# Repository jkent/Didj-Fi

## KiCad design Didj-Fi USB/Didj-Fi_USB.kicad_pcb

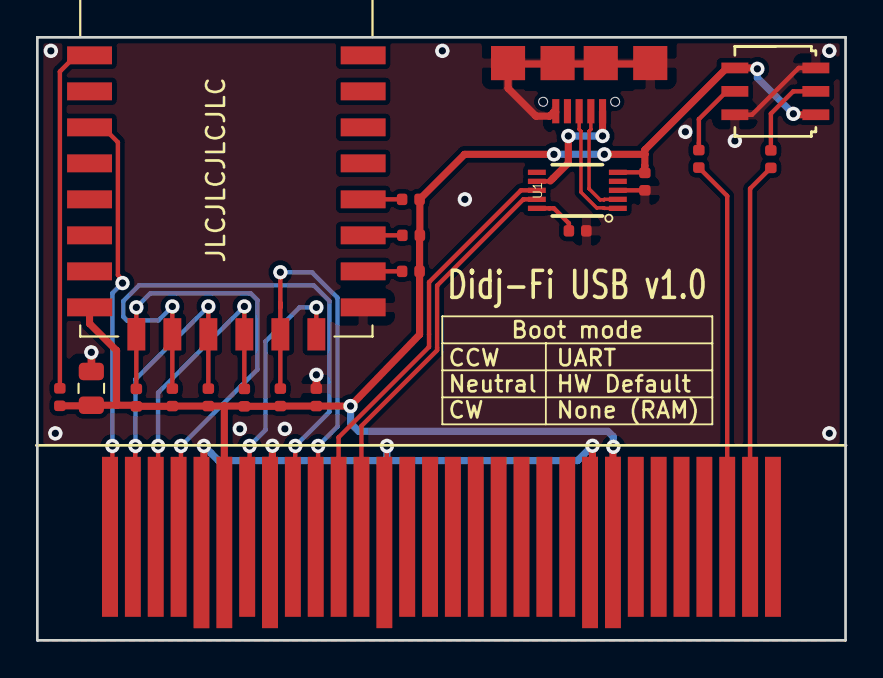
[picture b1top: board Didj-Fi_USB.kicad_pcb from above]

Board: 2 copper layers, 44.9 x 33.5 mm, 20 parts (0 on the bottom side), 23 nets.

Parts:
C1, C2, C4: 0.1u; C_0402_1005Metric
C3: 22u; C_0805_2012Metric
J1: didj_cart
J3: USB_B_Micro; C40942
R1, R3, R4, R5, R7, R8, R9, R11: 10k; R_0402_1005Metric
R2, R10: 4.7k; R_0402_1005Metric
R6: 3k; R_0402_1005Metric
S1: CS-4-22YA; cs-4
U1: CH340E; MSOP10
U2: ESP-12F; ESP-12E

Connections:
+3V3: C1.1, C3.1, C4.1, J1.6, J1.23, R1.1, R3.1, R4.1, R5.1, R6.1, R7.1, R8.1, R9.1, R11.1, S1.2, S1.~2, U1.5, U2.8
/CLK: J1.7, U2.14
/CMD: J1.4, R6.2, U2.9
/D5: J1.28, R2.2
/D6: J1.29, R10.1
/D+: J3.3, U1.1
/D-: J3.2, U1.2
/DAT0: J1.9, R3.2, U2.10
/DAT1: J1.10, R7.2, U2.13
/DAT2: J1.2, R4.2, U2.11
/DAT3: J1.3, R8.2, U2.12
/EN: J1.1, U2.3
/GPIO0: R11.2, U2.18
/GPIO2: R1.2, U2.17
/GPIO15: R9.2, U2.16
/RX: J1.11, U1.8
/TX: J1.12, U1.9
/V3: C2.1, U1.10
/~RST: R5.2, U2.1
GND: C1.2, C2.2, C3.2, C4.2, J1.5, J1.8, J1.13, J1.22, J3.5, J3.6, S1.1, S1.~1, U1.3, U2.15
unnamed: R2.1, S1.C
unnamed: R10.2, S1.~C
VBUS: J3.1, U1.7

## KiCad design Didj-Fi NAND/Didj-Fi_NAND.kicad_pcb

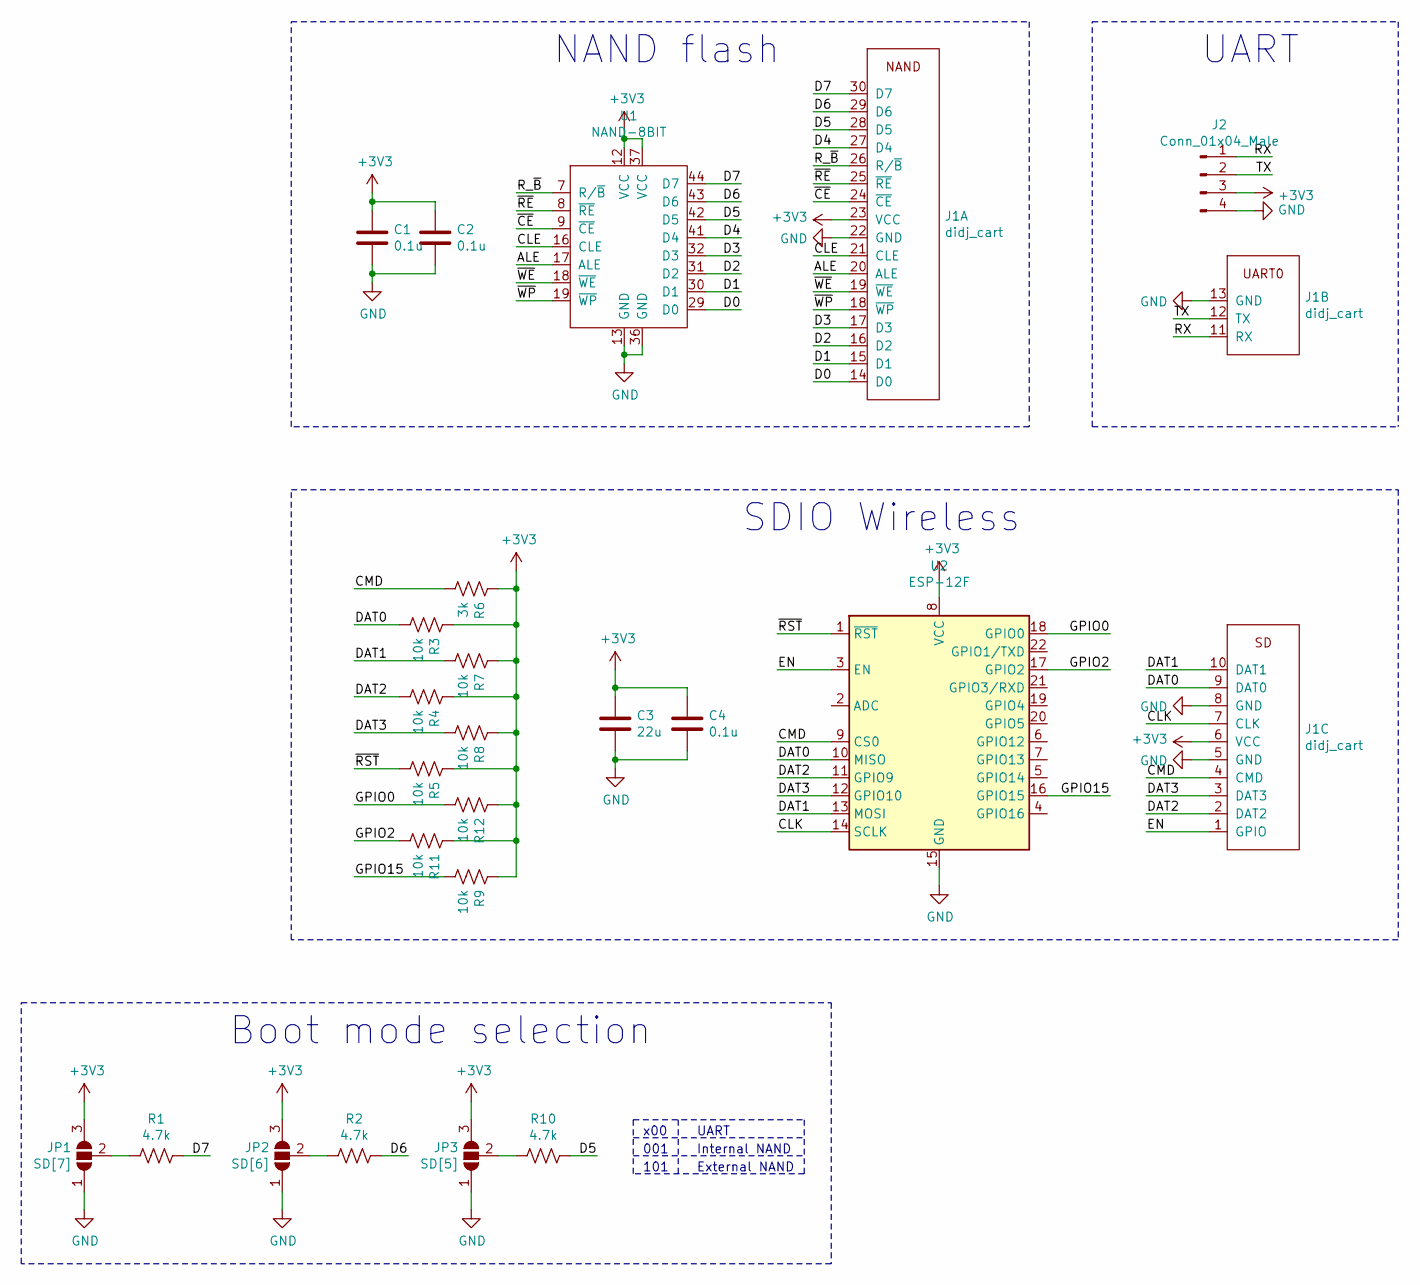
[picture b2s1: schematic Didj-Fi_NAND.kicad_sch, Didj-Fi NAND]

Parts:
C1, C2, C4: 0.1u; C_0402_1005Metric; LCSC C309458
C3: 22u; C_0805_2012Metric; LCSC C45783
J1: didj_cart
J2: Conn_01x04_Male; PinHeader_1x04_P2.54mm_Horizontal
JP1: SD[7]; SolderJumper-3_P1.3mm_Open_RoundedPad1.0x1.5mm
JP2: SD[6]; SolderJumper-3_P1.3mm_Open_RoundedPad1.0x1.5mm
JP3: SD[5]; SolderJumper-3_P1.3mm_Open_RoundedPad1.0x1.5mm
R1, R2, R10: 4.7k; R_0402_1005Metric; LCSC C25900
R3, R4, R5, R7, R8, R9, R11, R12: 10k; R_0402_1005Metric; LCSC C25744
R6: 3k; R_0402_1005Metric; LCSC C25784
U1: NAND-8BIT; TSOP48; LCSC C117899
U2: ESP-12F; ESP-12E

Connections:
+3V3: C1.1, C2.1, C3.1, C4.1, J1.6 (VCC), J1.23 (VCC), J2.3, JP1.3 (B), JP2.3 (B), JP3.3 (B), R3.1, R4.1, R5.1, R6.1, R7.1, R8.1, R9.1, R11.1, R12.1, U1.12 (VCC), U1.37 (VCC), U2.8 (VCC)
/ALE: J1.20 (ALE), U1.17 (ALE)
/CLE: J1.21 (CLE), U1.16 (CLE)
/CLK: J1.7 (CLK), U2.14 (SCLK)
/CMD: J1.4 (CMD), R6.2, U2.9 (CS0)
/D0: J1.14 (D0), U1.29 (D0)
/D1: J1.15 (D1), U1.30 (D1)
/D2: J1.16 (D2), U1.31 (D2)
/D3: J1.17 (D3), U1.32 (D3)
/D4: J1.27 (D4), U1.41 (D4)
/D5: J1.28 (D5), R10.1, U1.42 (D5)
/D6: J1.29 (D6), R2.1, U1.43 (D6)
/D7: J1.30 (D7), R1.1, U1.44 (D7)
/DAT0: J1.9 (DAT0), R3.2, U2.10 (MISO)
/DAT1: J1.10 (DAT1), R7.2, U2.13 (MOSI)
/DAT2: J1.2 (DAT2), R4.2, U2.11 (GPIO9)
/DAT3: J1.3 (DAT3), R8.2, U2.12 (GPIO10)
/EN: J1.1 (GPIO), U2.3 (EN)
/GPIO0: R12.2, U2.18 (GPIO0)
/GPIO2: R11.2, U2.17 (GPIO2)
/GPIO15: R9.2, U2.16 (GPIO15)
/RX: J1.11 (RX), J2.1
/R_~B: J1.26 (R/~B), U1.7 (R/~B)
/TX: J1.12 (TX), J2.2
/~CE: J1.24 (~CE), U1.9 (~CE)
/~RE: J1.25 (~RE), U1.8 (~RE)
/~RST: R5.2, U2.1 (~RST)
/~WE: J1.19 (~WE), U1.18 (~WE)
/~WP: J1.18 (~WP), U1.19 (~WP)
GND: C1.2, C2.2, C3.2, C4.2, J1.5 (GND), J1.8 (GND), J1.13 (GND), J1.22 (GND), J2.4, JP1.1 (A), JP2.1 (A), JP3.1 (A), U1.13 (GND), U1.36 (GND), U2.15 (GND)
unnamed: JP1.2 (C), R1.2
unnamed: JP2.2 (C), R2.2
unnamed: JP3.2 (C), R10.2

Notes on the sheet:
UART
101
001
x00
SDIO Wireless
Internal NAND
Boot mode selection
NAND flash
External NAND

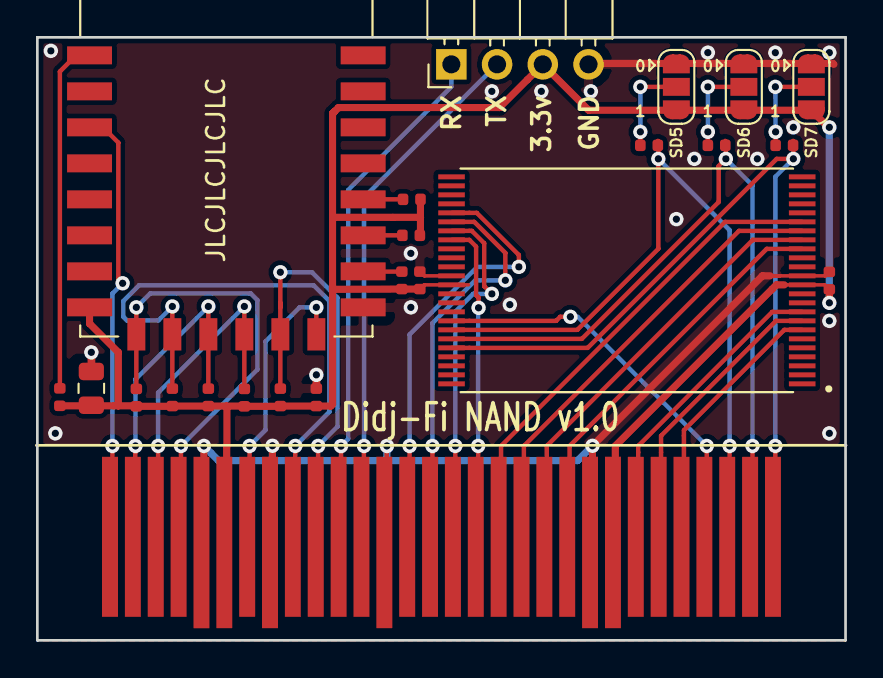
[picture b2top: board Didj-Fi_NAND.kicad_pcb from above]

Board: 2 copper layers, 44.9 x 33.5 mm, 23 parts (0 on the bottom side), 33 nets.

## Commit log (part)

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2020-05-25 minor tweaks
    removed an extra via
    re-routed a couple of traces
2020-05-25 silk screen changes
2020-05-25 change usb footprint
2020-05-26 prepare for manufacture
2020-05-26 solder mask tweak on Didj-Fi
2023-08-18 Create LICENSE
